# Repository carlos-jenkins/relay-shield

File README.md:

Advanced Relay Shield for Spark Core
====================================

[Spark Core] [] is a open source hardware Arduino compatible tiny Wi-Fi
development board that makes it easy to create internet-connected hardware.
This shield allows the Spark Core to control a high-power AC device and sense
the current flow.

Features
--------

  - Rated up to 220VAC @ 20A (4400W) ([part] [1]).
  - Current sensing using a CT sensor ([part] [2]).
  - Manual switch.
  - Panel/box ready.

Schematic
---------

[Schematic in PDF] [].

PCB
---

[PCB on OSHPark] [].

License
-------

Copyright (C) 2013 Carlos Jenkins <carlos@jenkins.co.cr>

This program is free software; you can redistribute it and/or modify
it under the terms of the GNU General Public License as published by
the Free Software Foundation; either version 2 of the License, or
(at your option) any later version.

This program is distributed in the hope that it will be useful,
but WITHOUT ANY WARRANTY; without even the implied warranty of
MERCHANTABILITY or FITNESS FOR A PARTICULAR PURPOSE.  See the
GNU General Public License for more details.

You should have received a copy of the GNU General Public License
along with this program.  If not, see <http://www.gnu.org/licenses/>.

  [1]: https://www.sparkfun.com/products/10924
  [2]: https://www.sparkfun.com/products/11005
  [Spark Core]: https://www.sparkdevices.com/
  [Schematic in PDF]: https://github.com/carlos-jenkins/relay-shield/raw/master/board/schematic/v1.0/relay_shield.pdf
  [PCB on OSHPark]: http://oshpark.com/shared_projects/E1XSjK44

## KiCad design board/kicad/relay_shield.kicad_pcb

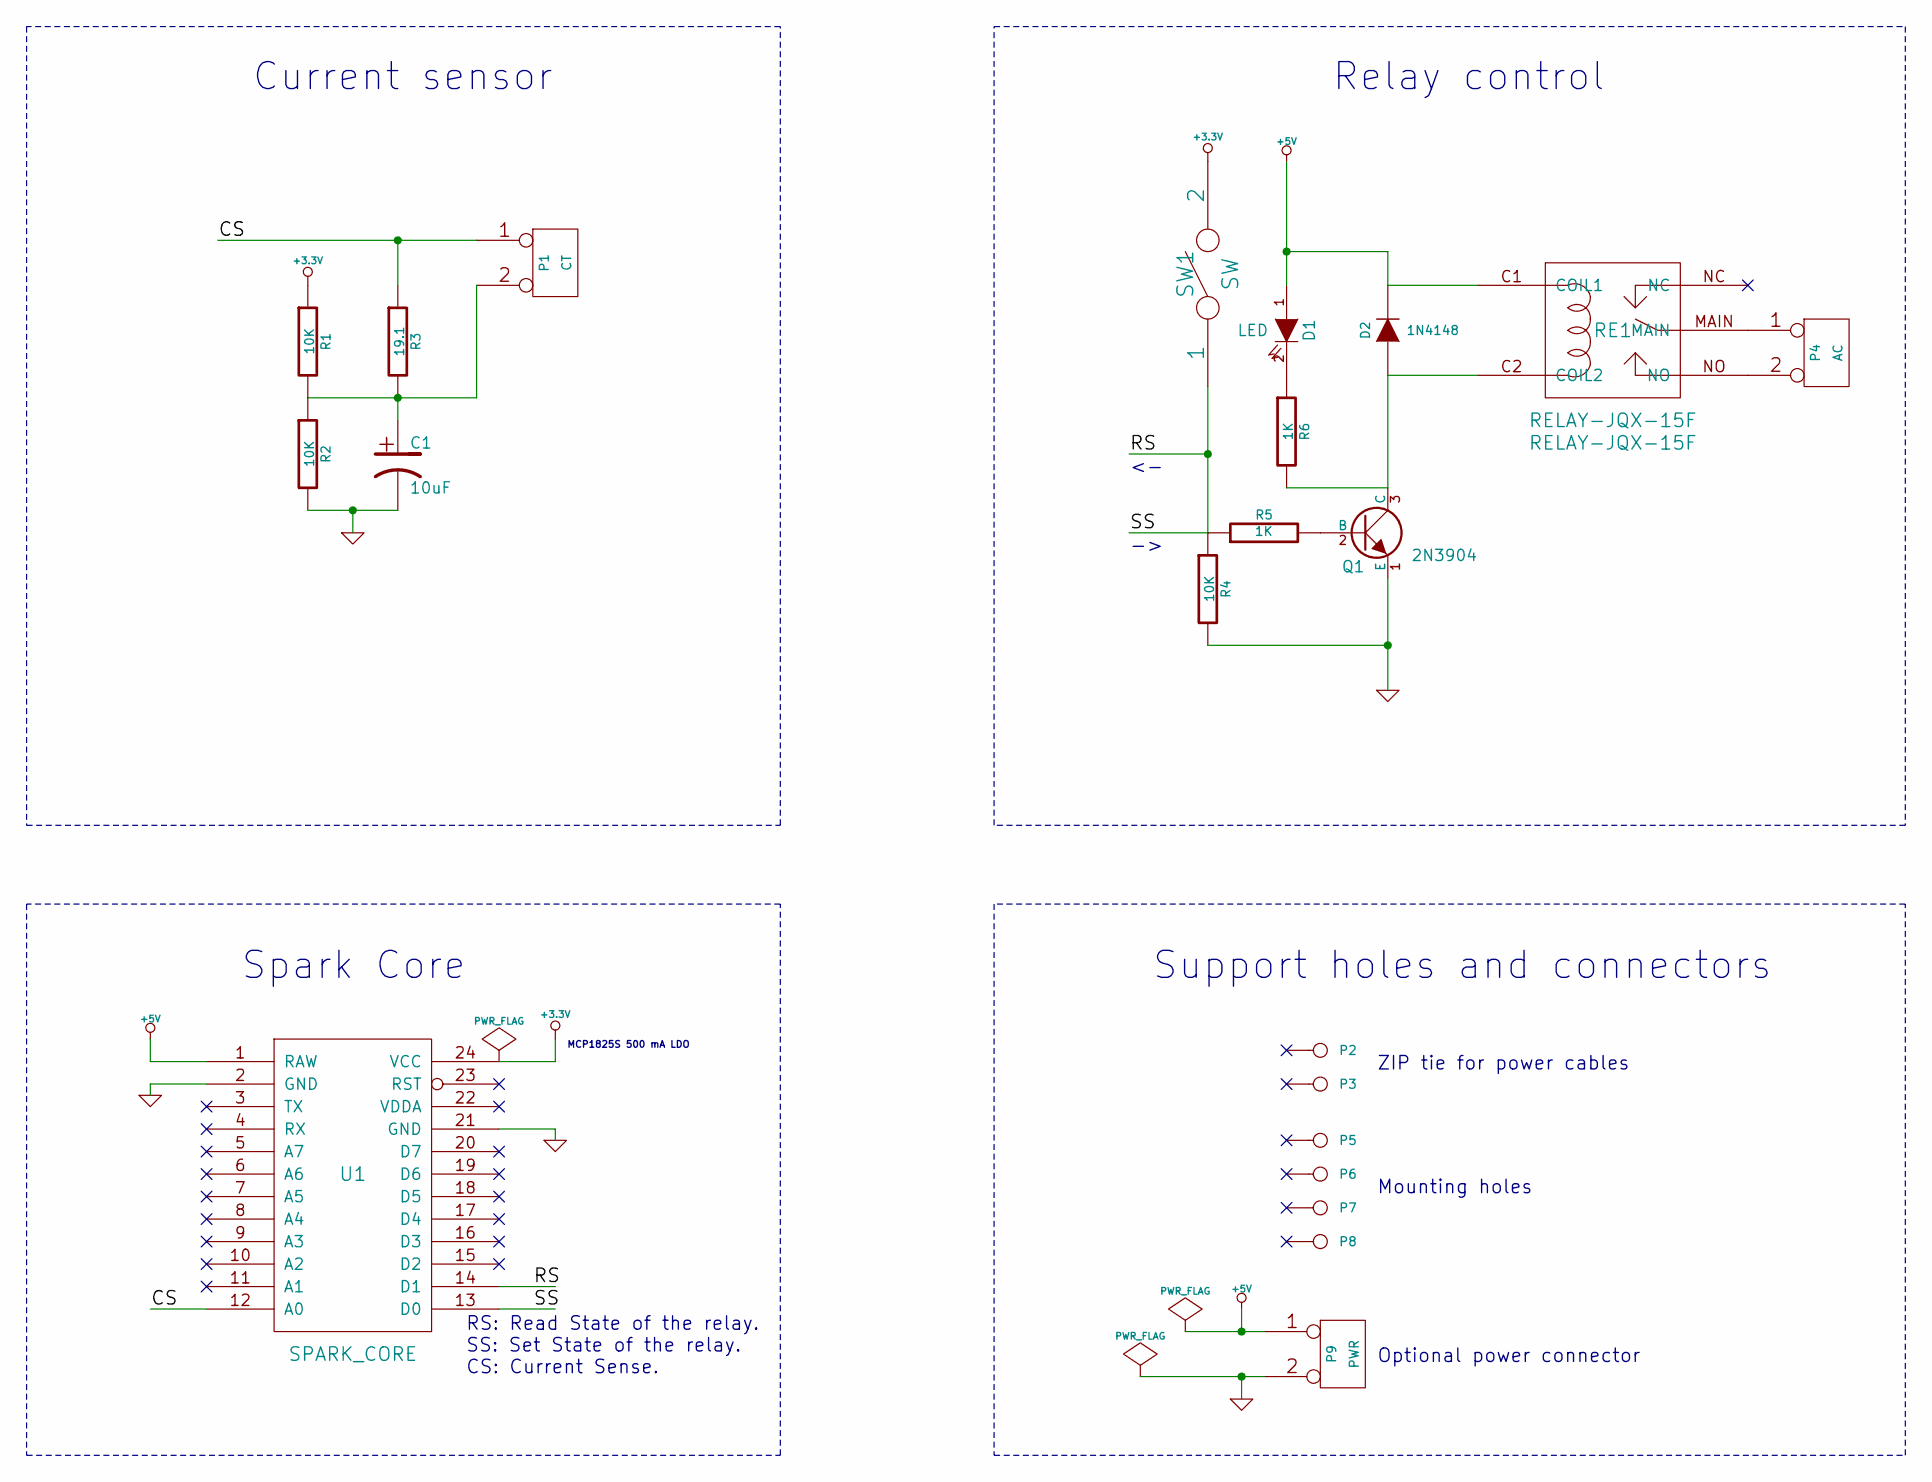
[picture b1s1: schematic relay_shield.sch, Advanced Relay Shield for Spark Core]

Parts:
C1: 10uF
D1: LED
D2: 1N4148
P1: CT
P2: Z1
P3: Z2
P4: AC
P5: MH1
P6: MH2
P7: MH3
P8: MH4
P9: PWR
Q1: 2N3904
R1, R2, R4: 10K
R3: 19.1
R5, R6: 1K
RE1: RELAY-JQX-15F
SW1: SW
U1: SPARK_CORE

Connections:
+3.3V: R1.1, SW1.2, U1.24 (VCC)
+5V: D1.1 (A), D2.2 (K), P9.1, RE1.C1 (COIL1), U1.1 (RAW)
/CS: P1.1, R3.1, U1.12 (A0)
/RS: R4.1, R5.1, SW1.1, U1.13 (D0), U1.14 (D1)
GND: C1.2, P9.2 (PM), Q1.1 (E), R2.2, R4.2, U1.2 (GND), U1.21 (GND)
unnamed: D2.1 (A), Q1.3 (C), R6.2, RE1.C2 (COIL2)
unnamed: C1.1, P1.2 (PM), R1.2, R2.1, R3.2
unnamed: P4.2 (PM), RE1.NO
unnamed: D1.2 (K), R6.1
unnamed: Q1.2 (B), R5.2
unnamed: P4.1, RE1.MAIN

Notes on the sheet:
RS: Read State of the relay. SS: Set State of the relay. CS: Current Sense.
MCP1825S 500 mA LDO
ZIP tie for power cables
Mounting holes
Support holes and connectors
Spark Core
Current sensor
Relay control
Optional power connector

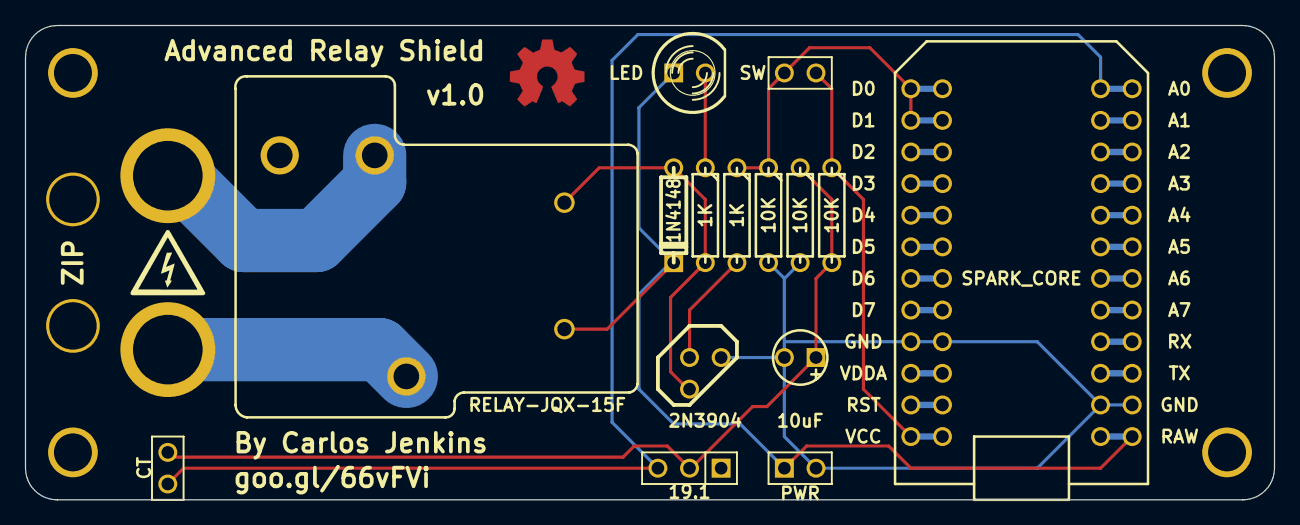
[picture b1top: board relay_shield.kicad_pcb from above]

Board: 2 copper layers, 100.3 x 38.1 mm, 25 parts (0 on the bottom side), 11 nets.

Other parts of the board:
OSHW: oshw_logo
OSHW_M: oshw_logo
WARN: high_voltage_logo

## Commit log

2013-08-13 First commit with repo structure.
2013-08-13 Ups, moved datasheets to it's folder.
2013-08-13 Added base KiCad project.
2013-08-13 Added Spark Core library/component.
2013-08-14 Optoisolator version. Not sure if to follow that path.
2013-08-14 Changed repository layout and added converted Eagle files.
2013-08-14 Finished schematic version 0.1.
2013-08-14 Forgot to add a connector for power.
2013-08-14 Base layout of the PCB.
2013-08-15 Finished to route the board.
2013-08-15 Normalized folders for version 0.1 and fixed some errors on Silkscreen.
2013-08-15 Fixed URL of the schematic image.
2013-08-15 Finished the Silkscreen.
2013-08-15 Added a PNG version of the gerbers.
2013-08-15 Added PCB to README.md.
2013-08-15 Almost final gerbers for production.
2013-08-16 Added render from OSHPark.
2013-08-16 Added link to OSHPark project.
2013-09-04 Added extra pads to allow connection to unused pins. Also fixed stand-offs size.
2013-09-04 Rolled out v1.0.
